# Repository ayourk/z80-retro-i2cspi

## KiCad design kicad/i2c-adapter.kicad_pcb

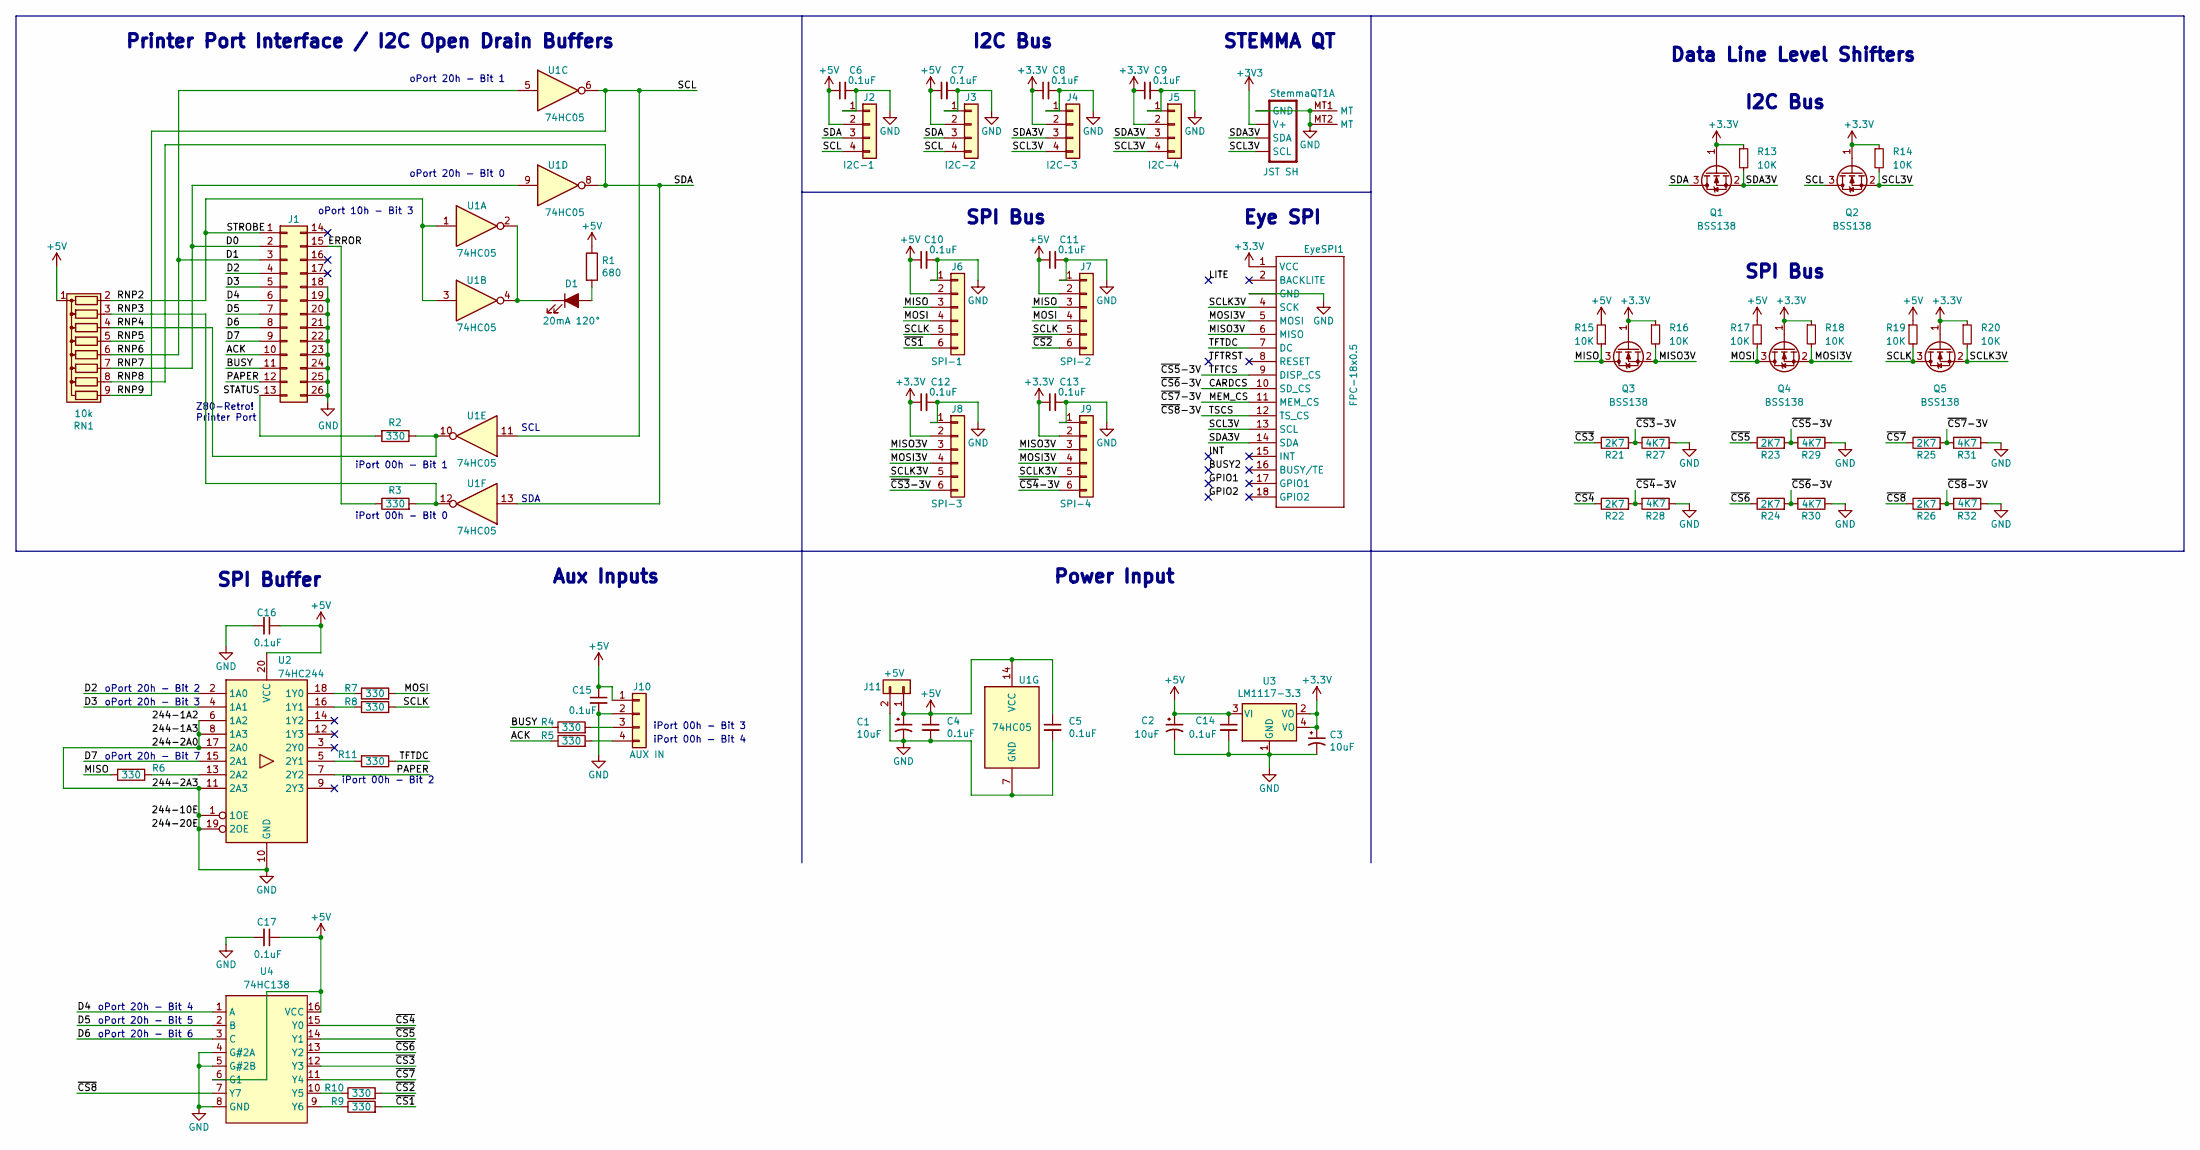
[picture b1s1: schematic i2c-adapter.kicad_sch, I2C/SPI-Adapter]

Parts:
C1: 10uF; C_0805_2012Metric_Pad1.18x1.45mm_HandSolder; MPN CL21B106KOQNNNE; LCSC C95841
C2, C3: 10uF; C_0805_2012Metric_Pad1.18x1.45mm_HandSolder; MPN CL21B106KOQNNNE; Digi-Key_PN 1276-2872-1-ND
C4, C5, C6, C7, C8, C9, C10, C11, C12, C13, C15, C16, C17: 0.1uF; C_0805_2012Metric_Pad1.18x1.45mm_HandSolder; MPN CL21B104KBFNNNE; LCSC C136621
C14: 0.1uF; C_0805_2012Metric_Pad1.18x1.45mm_HandSolder; MPN CL21B104KBFNNNE; Digi-Key_PN 1276-1180-1-ND
D1: 20mA 120°; LED_0805_2012Metric_Pad1.15x1.40mm_HandSolder; MPN 0805YGBD008S01; LCSC C375546
EyeSPI1: FPC-18x0.5; EYE_SPI_DISPLAY_BOTCONTACT; MPN TF31-18S-0.5SH(800); LCSC C2856802
J1: Conn_02x13_Top_Bottom; PinSocket_2x13_P2.54mm_Vertical; MPN CES-113-02-T-D; Digi-Key_PN SAM15543-ND
J2: I2C-1; PinSocket_1x04_P2.54mm_Vertical; MPN SL-104-TT-19; Digi-Key_PN SAM15257-ND
J3: I2C-2; PinSocket_1x04_P2.54mm_Vertical; MPN SL-104-TT-19; Digi-Key_PN SAM15257-ND
J4: I2C-3; PinSocket_1x04_P2.54mm_Vertical; MPN SL-104-TT-19; Digi-Key_PN SAM15257-ND
J5: I2C-4; PinSocket_1x04_P2.54mm_Vertical; MPN SL-104-TT-19; Digi-Key_PN SAM15257-ND
J6: SPI-1; PinSocket_1x06_P2.54mm_Vertical; MPN SL-106-TT-19; Digi-Key_PN SL-106-TT-19-ND
J7: SPI-2; PinSocket_1x06_P2.54mm_Vertical; MPN SL-106-TT-19; Digi-Key_PN SL-106-TT-19-ND
J8: SPI-3; PinSocket_1x06_P2.54mm_Vertical; MPN SL-106-TT-19; Digi-Key_PN SL-106-TT-19-ND
J9: SPI-4; PinSocket_1x06_P2.54mm_Vertical; MPN SL-106-TT-19; Digi-Key_PN SL-106-TT-19-ND
J10: AUX IN; PinHeader_1x04_P2.54mm_Vertical; MPN TSW-104-07-T-S; Digi-Key_PN SAM1035-04-ND
J11: +5V; PinHeader_1x02_P2.54mm_Vertical; MPN TSW-102-07-T-S; Digi-Key_PN SAM1035-02-ND
Q1, Q2, Q3, Q4, Q5: BSS138; SOT-23; MPN BSS138K; LCSC C255592
R1: 680; R_0805_2012Metric_Pad1.20x1.40mm_HandSolder; MPN ERJ-6ENF6800V; LCSC C410034
R2, R3, R4, R5, R6, R7, R8, R9, R10, R11: 330; R_0805_2012Metric_Pad1.20x1.40mm_HandSolder; MPN ERJ-6ENF3300V; LCSC C410007
R13, R14, R15, R16, R17, R18, R19, R20: 10K; R_0805_2012Metric_Pad1.20x1.40mm_HandSolder; MPN ERJ-6ENF1002V; Digi-Key_PN P10.0KCCT-ND
R21, R22, R23, R24, R25, R26: 2K7; R_0805_2012Metric_Pad1.20x1.40mm_HandSolder; MPN ERJ-6ENF2701V; LCSC C409999
R27, R28, R29, R30, R31, R32: 4K7; R_0805_2012Metric_Pad1.20x1.40mm_HandSolder; MPN ERJ-6ENF4701V; LCSC C192064
RN1: 10k; R_Array_SIP9; MPN 4309R-101-100LF; Digi-Key_PN 118-4309R-101-100LF-ND
StemmaQT1: JST SH; JST_SH4; MPN SM04B-SRSS-TB(LF)(SN); LCSC C2764183
U1: 74HC05; DIP-14_W7.62mm_Socket; MPN SN74HC05N; Digi-Key_PN 296-1568-5-ND
U2: 74HC244; DIP-20_W7.62mm_Socket; MPN SN74HC244N; Digi-Key_PN 296-1582-5-ND
U3: LM1117-3.3; SOT-223; MPN NCP1117ST33T3G; Digi-Key_PN NCP1117ST33T3GOSCT-ND
U4: 74HC138; DIP-16_W7.62mm_Socket; MPN SN74HC138N; Digi-Key_PN 296-1575-5-ND

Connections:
+5V: C1.1, C2.1, C4.1, C5.1, C6.1, C7.1, C10.1, C11.1, C14.1, C15.1, C16.1, C17.1, J2.2, J3.2, J6.2, J7.2, J10.1, J11.1, R1.1, R15.2, R17.2, R19.1, RN1.1 (common), U1.14 (VCC), U2.20 (VCC), U3.3 (VI), U4.6 (G1), U4.16 (VCC)
/ACK: J1.10, R5.1
/BUSY: J1.11, R4.1
/CARDCS: EyeSPI1.10 (SD_CS), R24.2, R30.2
/D0: J1.2, RN1.7 (R6), U1.9
/D1: J1.3, RN1.6 (R5), U1.5
/D2: J1.4, U2.2 (1A0)
/D3: J1.5, U2.4 (1A1)
/D4: J1.6, U4.1 (A)
/D5: J1.7, U4.2 (B)
/D6: J1.8, U4.3 (C)
/D7: J1.9, U2.15 (2A1)
/ERROR: J1.15, R3.1
/MEM_CS: EyeSPI1.11 (MEM_CS), R25.2, R31.1
/MISO: J6.3, J7.3, Q3.3 (D), R6.2, R15.1
/MISO3V: EyeSPI1.6 (MISO), J8.3, J9.3, Q3.2 (S), R16.2
/MOSI: J6.4, J7.4, Q4.3 (D), R7.2, R17.1
/MOSI3V: EyeSPI1.5 (MOSI), J8.4, J9.4, Q4.2 (S), R18.2
/PAPER: J1.12, U2.7 (2Y2)
/RNP2: J1.1, RN1.2 (R1), U1.1, U1.3
/RNP3: R3.2, RN1.3 (R2), U1.12
/RNP4: R2.1, RN1.4 (R3), U1.10
/RNP5: RN1.5 (R4)
/RNP8: J2.3, J3.3, Q1.3 (D), RN1.8 (R7), U1.8, U1.13
/RNP9: J2.4, J3.4, Q2.3 (D), RN1.9 (R8), U1.6, U1.11
/SCL3V: EyeSPI1.13 (SCL), J4.4, J5.4, Q2.2 (S), R14.2, StemmaQT1.4 (SCL)
/SCLK: J6.5, J7.5, Q5.3 (D), R8.2, R19.2
/SCLK3V: EyeSPI1.4 (SCK), J8.5, J9.5, Q5.2 (S), R20.2
/SDA3V: EyeSPI1.14 (SDA), J4.3, J5.3, Q1.2 (S), R13.2, StemmaQT1.3 (SDA)
/STATUS: J1.13, R2.2
/TFTCS: EyeSPI1.9 (DISP_CS), R23.2, R29.2
/TFTDC: EyeSPI1.7 (DC), R11.1
/TSCS: EyeSPI1.12 (TS_CS), R26.2, R32.2
/~CS1: J6.6, R9.2
/~CS2: J7.6, R10.2
/~CS3: R21.1, U4.12 (Y3)
/~CS3-3V: J8.6, R21.2, R27.1
/~CS4: R22.1, U4.15 (Y0)
/~CS4-3V: J9.6, R22.2, R28.2
/~CS5: R23.1, U4.14 (Y1)
/~CS6: R24.1, U4.13 (Y2)
/~CS7: R25.1, U4.11 (Y4)
/~CS8: R26.1, U4.7 (Y7)
GND: C1.2, C2.2, C3.2, C4.2, C5.2, C6.2, C7.2, C8.2, C9.2, C10.2, C11.2, C12.2, C13.2, C14.2, C15.2, C16.2, C17.2, EyeSPI1.3 (GND), EyeSPI1.SUPPORT1 (GND), EyeSPI1.SUPPORT2 (GND), J1.18, J1.19, J1.20, J1.21, J1.22, J1.23, J1.24, J1.25, J1.26, J2.1, J3.1, J4.1, J5.1, J6.1, J7.1, J8.1, J9.1, J10.2, J11.2, R27.2, R28.1, R29.1, R30.1, R31.2, R32.1, StemmaQT1.1 (GND), StemmaQT1.MT1 (MT), StemmaQT1.MT2 (MT), U1.7 (GND), U2.1 (1OE), U2.6 (1A2), U2.8 (1A3), U2.10 (GND), U2.11 (2A3), U2.17 (2A0), U2.19 (2OE), U3.1 (GND), U4.4 (G#2A), U4.5 (G#2B), U4.8 (GND)
unnamed: D1.1 (K), U1.2, U1.4
unnamed: D1.2 (A), R1.2
unnamed: J10.3, R4.2
unnamed: J10.4, R5.2
unnamed: R6.1, U2.13 (2A2)
unnamed: R7.1, U2.18 (1Y0)
unnamed: R8.1, U2.16 (1Y1)
unnamed: R9.1, U4.9 (Y6)
unnamed: R10.1, U4.10 (Y5)
unnamed: R11.2, U2.5 (2Y1)

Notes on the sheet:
iPort 00h - Bit 0
oPort 20h - Bit 3
oPort 20h - Bit 5
oPort 20h - Bit 1
Data Line Level Shifters
oPort 20h - Bit 0
oPort 10h - Bit 3
Printer Port Interface / I2C Open Drain Buffers
Z80-Retro! Printer Port
oPort 20h - Bit 2
oPort 20h - Bit 7
SPI Bus
oPort 20h - Bit 6
I2C Bus
oPort 20h - Bit 4
SCL
STEMMA QT
Power Input
Aux Inputs
iPort 00h - Bit 4
Eye SPI
iPort 00h - Bit 3
iPort 00h - Bit 2
SDA
SPI Buffer
iPort 00h - Bit 1

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
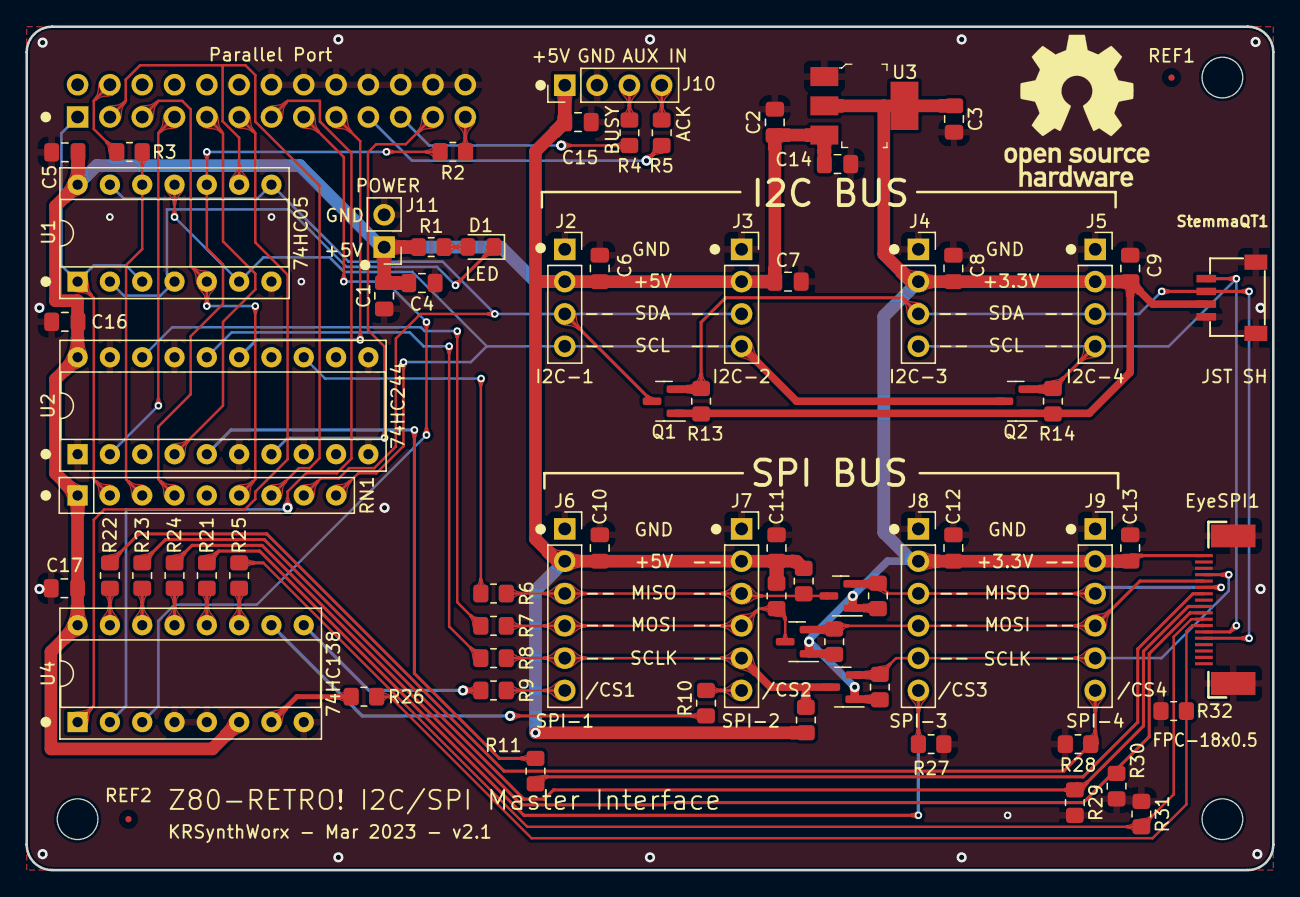
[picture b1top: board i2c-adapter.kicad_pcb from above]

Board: 2 copper layers, 98.0 x 66.3 mm, 74 parts (1 on the bottom side), 54 nets.

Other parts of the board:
REF1, REF2: Fiducial_0.5mm_Mask1.5mm

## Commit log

2023-04-11 With the help of @K3130440, I've added level shifters to the 3V3 data lines and a 74HC138 which adds more Chip Select lines (that are then routed to the EyeSPI connector). Updated Schematic PDF to in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
2023-04-12 Updated BOM. Most parts are available from both LCSC and DigiKey. Added Teardrops to PCB.
2023-04-18 Enhanced 3D Models and render; Moved away from Tantalum footprint.
